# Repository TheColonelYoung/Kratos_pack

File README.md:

# Kratos pack
Battery case with electronics for charging and protection of battery cells. Composes of 2s li-ion 3,7V battery cells. Includes undervoltage, overvoltage and overcurrent protection. As well as reverse voltage protection. Is charged from USB type-C connector. Support statistics over USB and have battery voltage indication via RGB LED.

 Front | Back |
-------------------------|-------------------------|
 | 

PCB is placed on top of batteries, so contact on bottom of board touch positive side of one battery and negative of other.
On other side batteries are connected only with metal bridge with spring contact to which is soldered cable which leads to connector on board. This wire is used to read voltage of individual batteries and balance then during charging.

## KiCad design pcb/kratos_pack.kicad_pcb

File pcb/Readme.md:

# PCB parameter
- 4 layer PCB
- 1 oz copper
- Minimal trace width 0.127 mm
- Via drilling 0.2, via copper 0.45 mm
- Thickness 1.6 mm
- Dimensions: 44.2 x 20.2 mm

# Connectors
### USB-C
- Supports USB 2.0
- Current up to 3A
- Bottom plastic bump for alignment should be removed to fit to board

### PROG connector
- Used to program STM32 microcontroller
- Contains SWD interface

### Debug connector
- Used to debug code in microcontroller
- Contains UART2 od microcontroller
- Pins: ground, RX, TX

### Battery connector
- Connects between batteries and to termistor
- Connect in midpoint of battery pack, used to sense voltage and ballance cells

### Output leads
- Solder pads for output wire
- Preferred connector on output is male XT30
- Output wire should be fixed with some type of strain relief

# Links
- 3 pin connectors 
    - Male [Mouser](https://mouser.com/ProductDetail/649-10114826-00003/)
    - Female [Mouser](https://mouser.com/ProductDetail/649-10114828-11103LF/)
    - Terminals [Mouser](https://mouser.com/ProductDetail/649-10114827-002LF/)
- Horizontal tactile switch [Mouser](https://mouser.com/ProductDetail/667-EVQP7J01P/)
- Tactile switches [Mouser](https://mouser.com/ProductDetail/611-KMT031NGJLHS/)
- LED 0606 [Mouser](https://mouser.com/ProductDetail/710-150066M153000/)
- LED Driver [Mouser](https://mouser.com/ProductDetail/389-KTD2026BEWETR/)

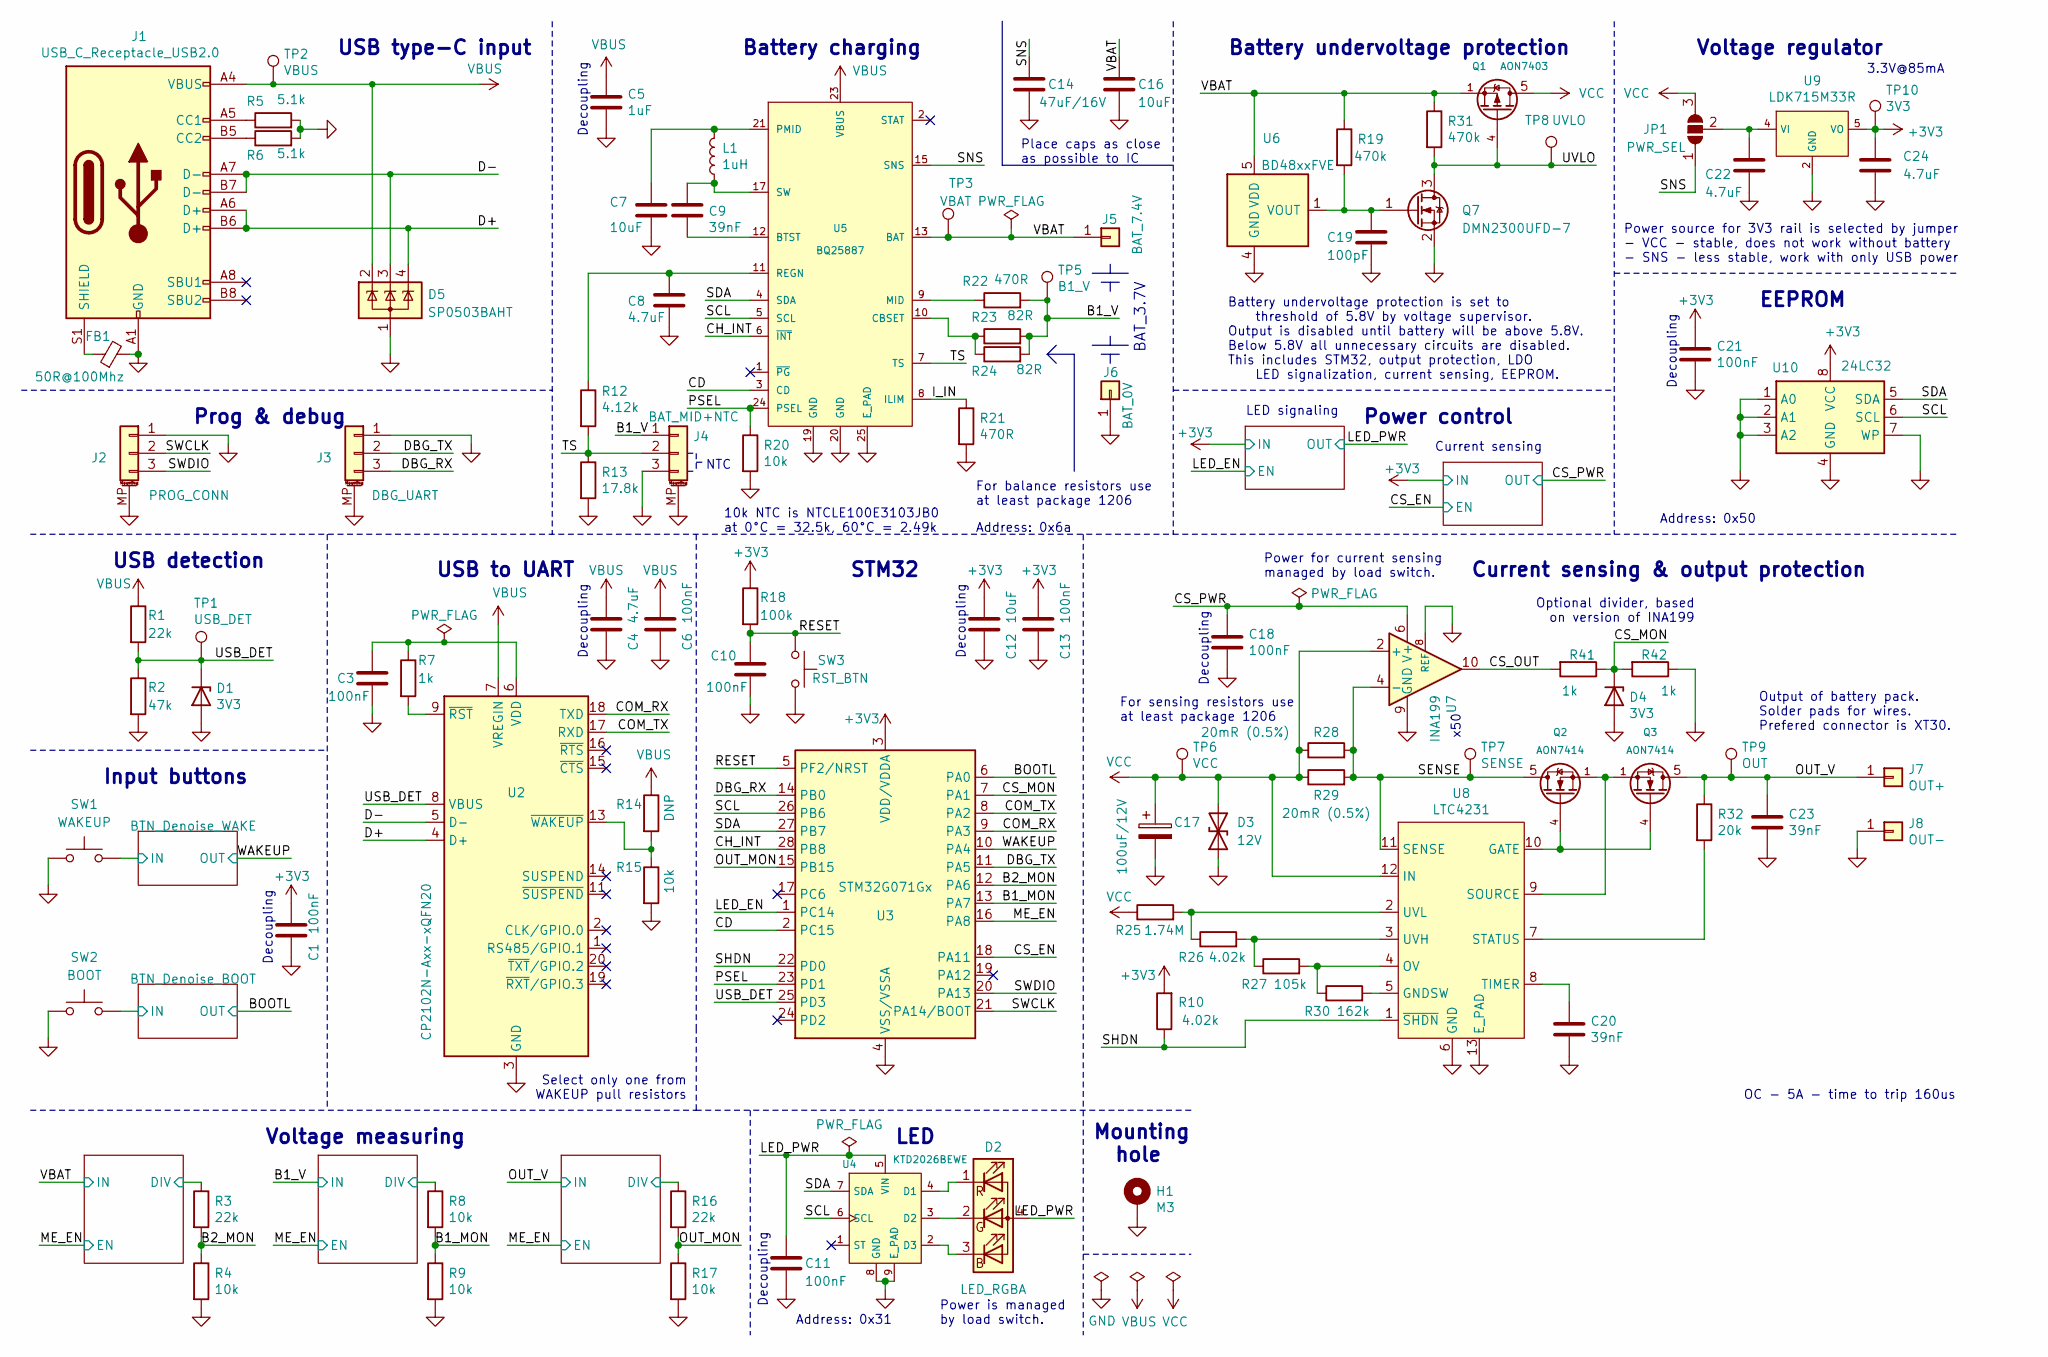
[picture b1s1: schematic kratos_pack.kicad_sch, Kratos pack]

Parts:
C1, C3, C6, C10, C11, C13, C18, C21: 100nF; C_0603_1608Metric
C4, C8, C22, C24: 4.7uF; C_0603_1608Metric
C5: 1uF; C_0603_1608Metric
C7, C12, C16: 10uF; C_0805_2012Metric
C9, C20, C23: 39nF; C_0603_1608Metric
C14: 47uF/16V; C_1206_3216Metric
C17: 100uF/12V; CP_EIA-7343-31_Kemet-D
C19: 100pF; C_0603_1608Metric
D1, D4: 3V3; D_SOD-523
D2: LED_RGBA; WL-SFCD - RGB606
D3: 12V; D_0603_1608Metric
D5: SP0503BAHT; SOT-143
FB1: 50R@100Mhz; L_1206_3216Metric
H1: M3; MountingHole_3.2mm_M3_Pad_Via
J1: USB_C_Receptacle_USB2.0; USB_C_Receptacle_HRO_TYPE-C-31-M-12
J2: PROG_CONN; Amphenol_10114828-11103LF_1x03_P1.25mm_Vertical
J3: DBG_UART; Amphenol_10114828-11103LF_1x03_P1.25mm_Vertical
J4: BAT_MID+NTC; Amphenol_10114828-11103LF_1x03_P1.25mm_Vertical
J5: BAT_7.4V; 18650_contact_bump
J6: BAT_0V; 18650_contact_bump
J7: OUT+; WirePad_SMD_1x_3x6mm
J8: OUT-; WirePad_SMD_1x_3x6mm
JP1: PWR_SEL; SolderJumper-3_P0.75mm_Open_Pad0.5x0.8mm
L1: 1uH; L_Taiyo-Yuden_MD-4040
Q1: AON7403; DFN-8-1EP_3x3mm_P0.65mm_EP1.55x2.4mm
Q2, Q3: AON7414; DFN-8-1EP_3x3mm_P0.65mm_EP1.55x2.4mm
Q7: DMN2300UFD-7; DFN-3_1.2x1.2mm
R1, R3, R16: 22k; R_0603_1608Metric
R2: 47k; R_0603_1608Metric
R4, R8, R9, R15, R17, R20: 10k; R_0603_1608Metric
R5, R6: 5.1k; R_0603_1608Metric
R7, R41, R42: 1k; R_0603_1608Metric
R10, R26: 4.02k; R_0603_1608Metric
R12: 4.12k; R_0603_1608Metric
R13: 17.8k; R_0603_1608Metric
R14: DNP; R_0603_1608Metric
R18: 100k; R_0603_1608Metric
R19, R31: 470k; R_0603_1608Metric
R21, R22: 470R; R_0603_1608Metric
R23, R24: 82R; R_1206_3216Metric
R25: 1.74M; R_0603_1608Metric
R27: 105k; R_0603_1608Metric
R28, R29: 20mR (0.5%); R_1206_3216Metric
R30: 162k; R_0603_1608Metric
R32: 20k; R_0603_1608Metric
SW1: WAKEUP; EVQ-P7J01P
SW2: BOOT; KMT031NGJLHS
SW3: RST_BTN; KMT031NGJLHS
TP1: USB_DET; TestPoint_Pad_D0.5mm
TP2: VBUS; TestPoint_Pad_D0.5mm
TP3: VBAT; TestPoint_Pad_D0.5mm
TP5: B1_V; TestPoint_Pad_D0.5mm
TP6: VCC; TestPoint_Pad_D0.5mm
TP7: SENSE; TestPoint_Pad_D0.5mm
TP8: UVLO; TestPoint_Pad_D0.5mm
TP9: OUT; TestPoint_Pad_D0.5mm
TP10: 3V3; TestPoint_Pad_D0.5mm
U2: CP2102N-Axx-xQFN20; SiliconLabs_QFN-20-1EP_3x3mm_P0.5mm_EP1.8x1.8mm
U3: STM32G071Gx; QFP-28_4x4_Pitch0.5mm
U4: KTD2026BEWE; UTDFN-8-1EP_1.5x1.5mm_P0.4mm_EP0.8x1.45mm
U5: BQ25887; QFN-24-1EP_4x4mm_P0.5mm_EP2.6x2.6mm
U6: BD48xxFVE; VSOF5
U7: INA199; UQFN-10_1.4x1.8mm_P0.4mm
U8: LTC4231; QFN-12-1EP_3x3mm_P0.5mm_EP1.65x1.65mm_ThermalVias
U9: LDK715M33R; SOT-23-5
U10: 24LC32; DFN-8-1EP_3x2mm_P0.5mm_EP1.3x1.5mm

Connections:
+3V3: C1.1, C12.1, C13.1, C21.1, C24.1, R10.2, R18.1, TP10.1, U3.3 (VDD/VDDA), U9.5 (VO), U10.8 (VCC); also elsewhere on the board
/B1_MON: R8.2, R9.1, U3.13 (PA7)
/B1_V: J4.1, R22.2, R23.2, R24.2, TP5.1; also elsewhere on the board
/B2_MON: R3.2, R4.1, U3.12 (PA6)
/BOOTL: U3.6 (PA0); also elsewhere on the board
/BTN_Denoise_BOOT/IN: SW2.2; also elsewhere on the board
/BTN_Denoise_WAKE/IN: SW1.2; also elsewhere on the board
/CD: U3.2 (PC15), U5.3 (CD)
/CH_INT: U3.28 (PB8), U5.6 (~INT)
/COM_RX: U2.18 (TXD), U3.9 (PA3)
/COM_TX: U2.17 (RXD), U3.8 (PA2)
/CS_EN: U3.18 (PA11); also elsewhere on the board
/CS_MON: D4.1 (K), R41.1, R42.2, U3.7 (PA1)
/CS_OUT: R41.2, U7.10
/CS_PWR: C18.1, U7.6 (V+); also elsewhere on the board
/D+: D5.4 (K), J1.A6 (D+), J1.B6 (D+), U2.4 (D+)
/D-: D5.3 (K), J1.A7 (D-), J1.B7 (D-), U2.5 (D-)
/DBG_RX: J3.3, U3.14 (PB0)
/DBG_TX: J3.2, U3.11 (PA5)
/I_IN: R21.1, U5.8 (ILIM)
/LED_EN: U3.1 (PC14); also elsewhere on the board
/LED_PWR: C11.1, D2.4 (A), U4.5 (VIN); also elsewhere on the board
/ME_EN: U3.16 (PA8); also elsewhere on the board
/OUT_MON: R16.2, R17.1, U3.15 (PB15)
/OUT_V: C23.1, J7.1, Q3.5 (D), Q3.6 (D), Q3.7 (D), Q3.8 (D), Q3.9 (D), R32.1, TP9.1; also elsewhere on the board
/PSEL: R20.1, U3.23 (PD1), U5.24 (PSEL)
/RESET: C10.1, R18.2, SW3.1, U3.5 (PF2/NRST)
/SCL: U3.26 (PB6), U4.6 (SCL), U5.5 (SCL), U10.6 (SCL)
/SDA: U3.27 (PB7), U4.7 (SDA), U5.4 (SDA), U10.5 (SDA)
/SENSE: Q2.5 (D), Q2.6 (D), Q2.7 (D), Q2.8 (D), Q2.9 (D), R28.2, R29.2, TP7.1, U7.4 (-), U7.5 (-), U8.11 (SENSE)
/SHDN: R10.1, U3.22 (PD0), U8.1 (~SHDN)
/SNS: C14.1, JP1.1 (A), U5.15 (SNS), U5.16 (SNS)
/SWCLK: J2.2, U3.21 (PA14/BOOT)
/SWDIO: J2.3, U3.20 (PA13)
/TS: J4.2, R12.2, R13.1, U5.7 (TS)
/USB_DET: D1.1 (K), R1.2, R2.1, TP1.1, U2.8 (VBUS), U3.25 (PD3)
/UVLO: Q1.4 (G), Q7.3 (D), R31.2, TP8.1
/VBAT: C16.1, J5.1, Q1.1 (S), Q1.2 (S), Q1.3 (S), R19.1, R31.1, TP3.1, U5.13 (BAT), U5.14 (BAT), U6.5 (VDD); also elsewhere on the board
/Voltage_measuring1/DIV: R8.1; also elsewhere on the board
/Voltage_measuring2/DIV: R16.1; also elsewhere on the board
/Voltage_measuring/DIV: R3.1; also elsewhere on the board
/WAKEUP: U3.10 (PA4); also elsewhere on the board
GND: C1.2, C3.2, C4.2, C5.2, C6.2, C7.2, C8.1, C10.2, C11.2, C12.2, C13.2, C14.2, C16.2, C17.2, C18.2, C19.2, C20.2, C21.2, C22.2, C23.2, C24.2, D1.2 (A), D3.1 (A1), D4.2 (A), D5.1 (A), FB1.2, H1.1, J1.A1 (GND), J1.A12 (GND), J1.B1 (GND), J1.B12 (GND), J2.1, J2.MP (MountPin), J3.1, J3.MP (MountPin), J4.3, J4.MP (MountPin), J6.1, J8.1, Q7.2 (S), R2.2, R4.2, R5.2, R6.2, R9.2, R13.2, R15.2, R17.2, R20.2, R21.2, R42.1, SW1.1, SW2.1, SW3.2, U2.3 (GND), U2.12 (GND), U2.21 (GND), U3.4 (VSS/VSSA), U4.8 (GND), U4.9 (E_PAD), U5.19 (GND), U5.20 (GND), U5.25 (E_PAD), U6.2 (GND), U6.4 (GND), U7.8 (REF), U7.9 (GND), U8.6 (GND), U8.13 (E_PAD), U9.2 (GND), U10.1 (A0), U10.2 (A1), U10.3 (A2), U10.4 (GND), U10.7 (WP); also elsewhere on the board
unnamed: C3.1, R7.1, U2.6 (VDD)
unnamed: C7.1, L1.2, U5.21 (PMID), U5.22 (PMID)
unnamed: C8.2, R12.1, U5.11 (REGN)
unnamed: C9.1, U5.12 (BTST)
unnamed: C9.2, L1.1, U5.17 (SW), U5.18 (SW)
unnamed: C19.1, Q7.1 (G), R19.2, U6.1 (VOUT)
unnamed: C20.1, U8.8 (TIMER)
unnamed: C22.1, JP1.2 (C), U9.4 (VI)
unnamed: D2.1 (RK), U4.4 (D1)
unnamed: D2.2 (GK), U4.3 (D2)
unnamed: D2.3 (BK), U4.2 (D3)
unnamed: FB1.1, J1.S1 (SHIELD)
unnamed: J1.A5 (CC1), R5.1
unnamed: J1.B5 (CC2), R6.1
unnamed: Q2.1 (S), Q2.2 (S), Q2.3 (S), Q3.1 (S), Q3.2 (S), Q3.3 (S), U8.9 (SOURCE)
unnamed: Q2.4 (G), Q3.4 (G), U8.10 (GATE)
unnamed: R7.2, U2.9 (~RST)
unnamed: R14.2, R15.1, U2.13 (~WAKEUP)
unnamed: R22.1, U5.9 (MID)
unnamed: R23.1, R24.1, U5.10 (CBSET)
unnamed: R25.2, R26.1, U8.2 (UVL)
unnamed: R26.2, R27.1, U8.3 (UVH)
unnamed: R27.2, R30.1, U8.4 (OV)
unnamed: R30.2, U8.5 (GNDSW)
unnamed: R32.2, U8.7 (STATUS)
VBUS: C4.1, C5.1, C6.1, D5.2 (K), J1.A4 (VBUS), J1.A9 (VBUS), J1.B4 (VBUS), J1.B9 (VBUS), R1.1, R14.1, TP2.1, U2.7 (VREGIN), U5.23 (VBUS)
VCC: C17.1, D3.2 (A2), JP1.3 (B), Q1.5 (D), Q1.6 (D), Q1.7 (D), Q1.8 (D), Q1.9 (D), R25.1, R28.1, R29.1, TP6.1, U7.2 (+), U7.3 (+), U8.12 (IN)

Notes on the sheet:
Decoupling
Address: 0x31
For sensing resistors use at least package 1206
Power control
OC - 5A - time to trip 160us
Current sensing
Address: 0x50
Power is managed by load switch.
LED
For balance resistors use at least package 1206
NTC
Output of battery pack. Solder pads for wires. Prefered connector is XT30.
USB type-C input
USB detection
Battery charging
Voltage regulator
Power source for 3V3 rail is selected by jumper - VCC - stable, does not work without battery - SNS - less stable, work with only USB power
x50
Prog & debug
LED signaling
Optional divider, based on version of INA199
Battery undervoltage protection is set to threshold of 5.8V by voltage supervisor. Output is disabled until battery will be above 5.8V. Below 5.8V all unnecessary circuits are disabled. This includes STM32, output protection, LDO LED signalization, current sensing, EEPROM.
BAT_3.7V
Select only one from WAKEUP pull resistors
3.3V@85mA
USB to UART
Address: 0x6a
10k NTC is NTCLE100E3103JB0 at 0°C = 32.5k, 60°C = 2.49k
Power for current sensing managed by load switch.
EEPROM
Current sensing & output protection
STM32
Place caps as close as possible to IC
Mounting hole
Input buttons
Voltage measuring
Battery undervoltage protection

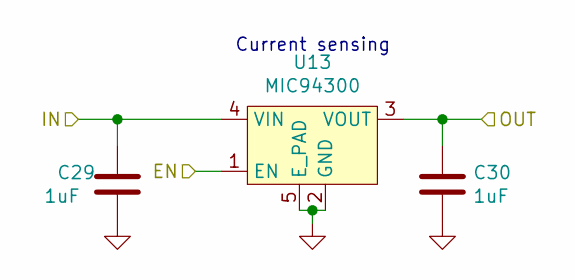
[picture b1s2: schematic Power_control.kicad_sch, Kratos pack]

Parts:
C29, C30: 1uF; C_0603_1608Metric
U13: MIC94300; MLF-4_1.2x1.6mm_P0.5_1EP_0.85x0.5mm

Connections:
+3V3: C29.1, U13.4 (VIN); also elsewhere on the board
/LED_EN: U13.1 (EN); also elsewhere on the board
/LED_PWR: C30.1, U13.3 (VOUT); also elsewhere on the board
GND: C29.2, C30.2, U13.2 (GND), U13.5 (E_PAD); also elsewhere on the board

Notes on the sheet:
Current sensing

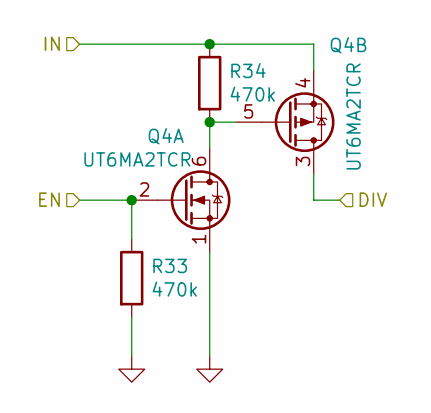
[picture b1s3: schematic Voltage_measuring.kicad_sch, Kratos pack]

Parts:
Q4: UT6MA2TCR; UDFN-6-2EP_2x2mm_P0.65mm_EP1x0.7mm
R33, R34: 470k; R_0603_1608Metric

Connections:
/ME_EN: Q4.2 (GN), R33.1; also elsewhere on the board
/VBAT: Q4.4 (SP), Q4.8 (SP), R34.1; also elsewhere on the board
/Voltage_measuring/DIV: Q4.3 (DP); also elsewhere on the board
GND: Q4.1 (SN), R33.2; also elsewhere on the board
unnamed: Q4.5 (GP), Q4.6 (DN), Q4.7 (DN), R34.2

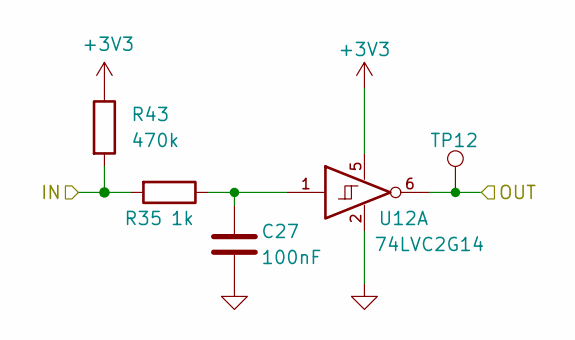
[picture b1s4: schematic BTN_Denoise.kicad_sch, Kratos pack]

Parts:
C27: 100nF; C_0603_1608Metric
R35: 1k; R_0603_1608Metric
R43: 470k; R_0603_1608Metric
TP12: TestPoint; TestPoint_Pad_D0.5mm
U12: 74LVC2G14; SOT-363_SC-70-6

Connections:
+3V3: R43.1, U12.5; also elsewhere on the board
/BOOTL: U12.4; also elsewhere on the board
/BTN_Denoise_WAKE/IN: R35.2, R43.2; also elsewhere on the board
/WAKEUP: TP12.1, U12.6; also elsewhere on the board
GND: C27.2, U12.2; also elsewhere on the board
unnamed: C27.1, R35.1, U12.1
unnamed 52: U12.3; also elsewhere on the board

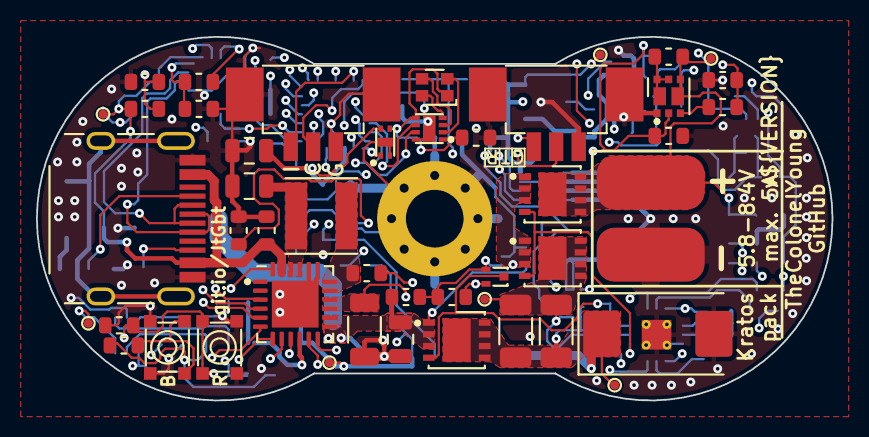
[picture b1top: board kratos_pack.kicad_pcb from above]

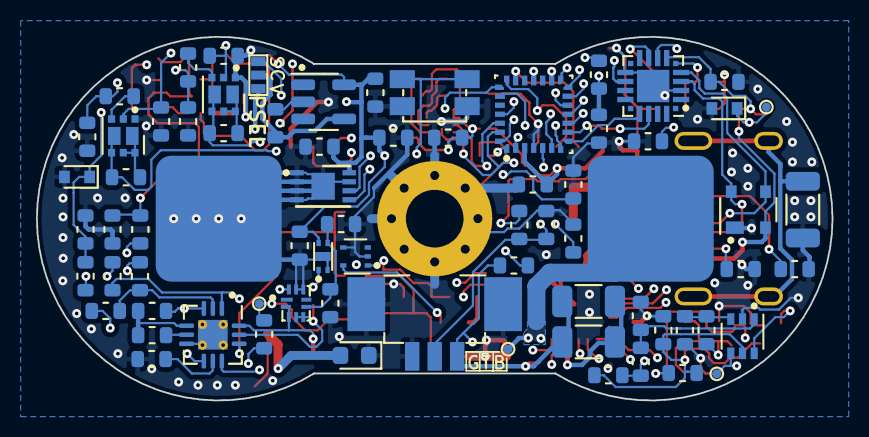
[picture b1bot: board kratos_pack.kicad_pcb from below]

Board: 4 copper layers, 44.2 x 20.2 mm, 121 parts (73 on the bottom side), 75 nets.

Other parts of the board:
C25, C26: 1uF; C_0603_1608Metric
C28: 100nF; C_0603_1608Metric
Q5, Q6: UT6MA2TCR; UDFN-6-2EP_2x2mm_P0.65mm_EP1x0.7mm
R36: 1k; R_0603_1608Metric
R37, R38, R39, R40, R44: 470k; R_0603_1608Metric
TP14: TestPoint; TestPoint_Pad_D0.5mm
U11: MIC94300; MLF-4_1.2x1.6mm_P0.5_1EP_0.85x0.5mm

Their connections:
+3V3: C25.1, R44.1, U11.4 (VIN); also elsewhere on the board
/B1_V: Q5.4 (SP), Q5.8 (SP), R38.1; also elsewhere on the board
/BOOTL: TP14.1; also elsewhere on the board
/BTN_Denoise_BOOT/IN: R36.2, R44.2; also elsewhere on the board
/CS_EN: U11.1 (EN); also elsewhere on the board
/CS_PWR: C26.1, U11.3 (VOUT); also elsewhere on the board
/ME_EN: Q5.2 (GN), Q6.2 (GN), R37.1, R39.1; also elsewhere on the board
/OUT_V: Q6.4 (SP), Q6.8 (SP), R40.1; also elsewhere on the board
/Voltage_measuring1/DIV: Q5.3 (DP); also elsewhere on the board
/Voltage_measuring2/DIV: Q6.3 (DP); also elsewhere on the board
GND: C25.2, C26.2, C28.2, Q5.1 (SN), Q6.1 (SN), R37.2, R39.2, U11.2 (GND), U11.5 (E_PAD); also elsewhere on the board
unnamed 52: C28.1, R36.1; also elsewhere on the board
unnamed: Q5.5 (GP), Q5.6 (DN), Q5.7 (DN), R38.2
unnamed: Q6.5 (GP), Q6.6 (DN), Q6.7 (DN), R40.2

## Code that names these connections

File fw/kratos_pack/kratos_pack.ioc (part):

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Mcu.Name=STM32G071G(6-8-B)Ux
Mcu.Package=UFQFPN28
Mcu.UserName=STM32G071GBUx
PA0.GPIOParameters=GPIO_Label
PA0.GPIO_Label=BOOT
PA0.Mode=SYS_WakeUp0
PA0.Signal=SYS_WKUP1
PA1.GPIOParameters=GPIO_Label
PA1.GPIO_Label=CS_MON
PA1.Mode=IN1
PA1.Signal=ADC1_IN1
PA11\ [PA9].GPIOParameters=GPIO_Label
PA11\ [PA9].GPIO_Label=CS_EN
PA11\ [PA9].Signal=GPIO_Output
PA13.Mode=Serial_Wire
PA13.Signal=SYS_SWDIO
PA14-BOOT0.Mode=Serial_Wire
PA14-BOOT0.Signal=SYS_SWCLK
PA2.Mode=Asynchronous
PA2.Signal=USART2_TX
PA3.Mode=Asynchronous
PA3.Signal=USART2_RX
PA4.GPIOParameters=GPIO_Label
PA4.GPIO_Label=WAKEUP
PA4.Mode=SYS_WakeUp1
PA4.Signal=SYS_WKUP2
PA5.Mode=Asynchronous
PA5.Signal=USART3_TX
PA6.GPIOParameters=GPIO_Label
PA6.GPIO_Label=B2_MON
PA6.Mode=IN6
PA6.Signal=ADC1_IN6
PA7.GPIOParameters=GPIO_Label
PA7.GPIO_Label=B1_MON
PA7.Mode=IN7
PA7.Signal=ADC1_IN7
PA8.GPIOParameters=GPIO_Label
PA8.GPIO_Label=ME_EN
PA8.Signal=GPIO_Output
PB0.Mode=Asynchronous
PB0.Signal=USART3_RX
PB1.GPIOParameters=GPIO_Label
PB1.GPIO_Label=OUT_MON
PB1.Mode=IN9
PB1.Signal=ADC1_IN9
PB3.GPIOParameters=GPIO_Label
PB3.GPIO_Label=PSEL
PB3.Signal=GPIO_Output
PB5.GPIOParameters=GPIO_Label
PB5.GPIO_Label=USD_DET
PB5.Mode=SYS_WakeUp6
PB5.Signal=SYS_WKUP6
PB6.Mode=I2C
PB6.Signal=I2C1_SCL
PB7.Mode=I2C
PB7.Signal=I2C1_SDA
PB8.GPIOParameters=GPIO_Label
PB8.GPIO_Label=CH_INT
PB8.Signal=GPXTI8
PC14-OSC32_IN\ (PC14).GPIOParameters=GPIO_Label
PC14-OSC32_IN\ (PC14).GPIO_Label=LED_EN
PC14-OSC32_IN\ (PC14).Signal=GPIO_Output
PC15-OSC32_OUT\ (PC15).GPIOParameters=GPIO_Label
PC15-OSC32_OUT\ (PC15).GPIO_Label=CD
PC15-OSC32_OUT\ (PC15).Signal=GPIO_Output
RCC.HSE_VALUE=8000000
RCC.SYSCLKFreq_VALUE=64000000
RCC.SYSCLKSource=RCC_SYSCLKSOURCE_PLLCLK
board=custom

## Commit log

2020-12-24 Schema: complete schematics of device
2021-01-12 Schema: bom optimization
2021-01-12 Schema: update footprint 3-pin connectors, project cleanup, add gitignore
2021-01-14 Schema: Remove unnecessary test points (switches) and filtering capacitors (STM, CP2102)
2021-01-14 PCB: Route USB input, charger circuit and switches
2021-01-14 Schema: add some connection STM32, remove redundant connections to BQ25887
2021-01-14 PCB: routing of mcu, voltage mesuring, part of current sensing and power regulator
2021-01-14 fw: add initial project configuration from CubeMX with MCU connections
2021-01-15 FW: add connections for voltage measuring to MCU
2021-01-15 Schema: add connections from MCU to voltage measuring circuits
2021-01-15 PCB: route power and voltage measuring
2021-01-15 FW: update connection of CS_EN pin
2021-01-15 Schema: update connection of CS_EN pin
2021-01-15 PCB: finalization of routing, add silk screen
2021-01-17 PCB: fix clearance based on JLCPCB capabilities
2021-01-17 BOM: update iBOM to new version of PCB
2021-01-25 FW: update pin mapping of MCU
2021-01-25 PCB: add 3D packages to parts
2021-01-25 PCB: update silk screen
2021-01-25 Schema: update page layout
2021-01-25 Add renders of board, updates readme, add pdf with schematics
2021-02-01 Schema & PCB: add pull up to wakeup button
2021-02-01 PCB: connector mounting point to ground, change LDk package to SOT-23-5
2022-06-21 FW: add application for I2C scanning and communication testing
2022-06-21 Schema: update page layout and add I2C addresses to I2C device
2022-06-21 PCB: update page layout and update to new version
2022-06-21 Errata: add datasheet describing errors in v1.0
2022-07-25 Errata: add note about signaling LED footprint
2022-07-25 Schema & PCB: reconect output of charger from SNS to VBAT
2022-07-25 PCB: change footprint of resistors and capacitors to smaller version
    After first version is apparent that smaller footprint used on some
    resistors are big enough for manual soldering. Because of this was
    exchanged for custom smaller version.
    In current version pull-up resistor of reset circuit is not connected,
    because is mend to be removed in future.
2022-07-25 Changelog: add changelog file with previously made modifications
2022-07-26 Schema & PCB: Remove resistor in series with RESET line
    Also some passive components around was shifter which resulted in better
    clearance from edge of PCB.
2022-07-26 Schema & PCB: exchange SNS capacitor of charger IC for 47uF/16V in 1206
2022-07-27 Schema & PCB: fix under-voltage supervisor by inverting output signal
2022-07-27 PCB: Fixed silkscreen overlapping issues (side button and USB connector)
2022-08-01 Schema & PCB: Fix USB detection by MCU and USB converter, hide GND labels
    USB detection circuit is now connected only to MCU.
    Converter from USB to UART (CP2102) is directly connected to VBUS.
2022-08-28 Schema: Removed intended ILIM connection, mirror connectors, fix typos
2022-08-28 PCB: Fix footprint of signalization LED
2023-02-02 Schema: fix USB connection
2023-02-02 Schema & PCB: connect LTC4231 Shutdown pin to MCU GPIO
2023-02-02 PCB: fix USB connection, change ESD protection IC
2023-02-02 Schema: fix incorrect MOSFET model in UVLO invertor
2023-02-02 Schema & PCB: add jumper selector for 3V3 rail regulator supply (VCC/SNS)
2023-02-02 Changelog & Errata: update for new version
2023-02-11 PCB: layout optimization (around LTC4231 and center mounting hole to GND)
2023-02-12 Schema: shorten UVLo connection to avoid confusion (compared to prev. ver.)
